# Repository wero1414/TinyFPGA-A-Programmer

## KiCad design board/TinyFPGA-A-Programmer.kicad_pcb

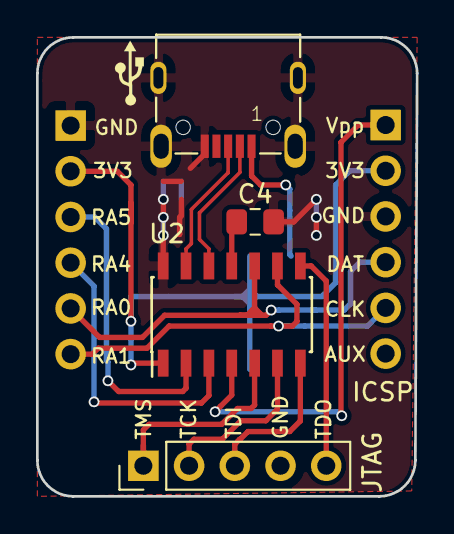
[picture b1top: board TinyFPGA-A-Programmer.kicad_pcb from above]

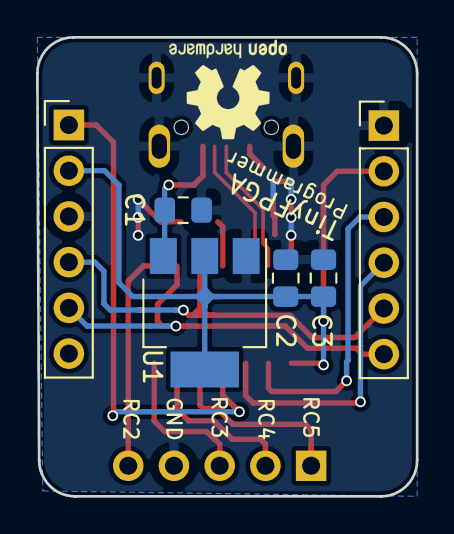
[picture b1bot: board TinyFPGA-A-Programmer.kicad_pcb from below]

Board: 2 copper layers, 21.1 x 25.5 mm, 11 parts (6 on the bottom side), 15 nets.

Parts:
C1, C2, C4: 1uF; C_0805_2012Metric_Pad1.15x1.40mm_HandSolder
C3: 100nF; C_0805_2012Metric_Pad1.15x1.40mm_HandSolder
J1: USB; 629105150521
J2: JTAG; PinHeader_1x05_P2.54mm_Vertical
J3: ICSP; PinHeader_1x06_P2.54mm_Vertical
J4: CONN_01X06; PinHeader_1x06_P2.54mm_Vertical
U1: AP1117-33; SOT-223-3_TabPin2
U2: PIC16F1455-ISL; SOIC-14_3.9x8.7mm_P1.27mm
svg2mod: G***; usb_graphic

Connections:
+3V3: C2.1, C3.1, J3.2, J4.2, U1.2, U2.1
+5V: C1.1, J1.1, U1.3
/D+: J1.3, U2.13
/D-: J1.2, U2.12
/RC2: J2.5, U2.8
/RC3: J2.3, U2.7
/RC4: J2.2, U2.6
/RC5: J2.1, U2.5
GND: C1.2, C2.2, C3.2, C4.1, J1.5, J1.6, J2.4, J3.3, J4.1, U1.1, U2.14
ICSPCLK: J3.5, J4.6, U2.9
ICSPDAT: J3.4, J4.5, U2.10
unnamed: C4.2, U2.11
RA4: J4.4, U2.3
RA5: J4.3, U2.2
VPP: J3.1, U2.4

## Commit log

2019-05-25 Change PIC footprint and shape
